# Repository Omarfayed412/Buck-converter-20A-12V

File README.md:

# Buck-converter-20A-12-V
DC DC step down buck converter 12v 20A  
Feel fee to contact me for the design files

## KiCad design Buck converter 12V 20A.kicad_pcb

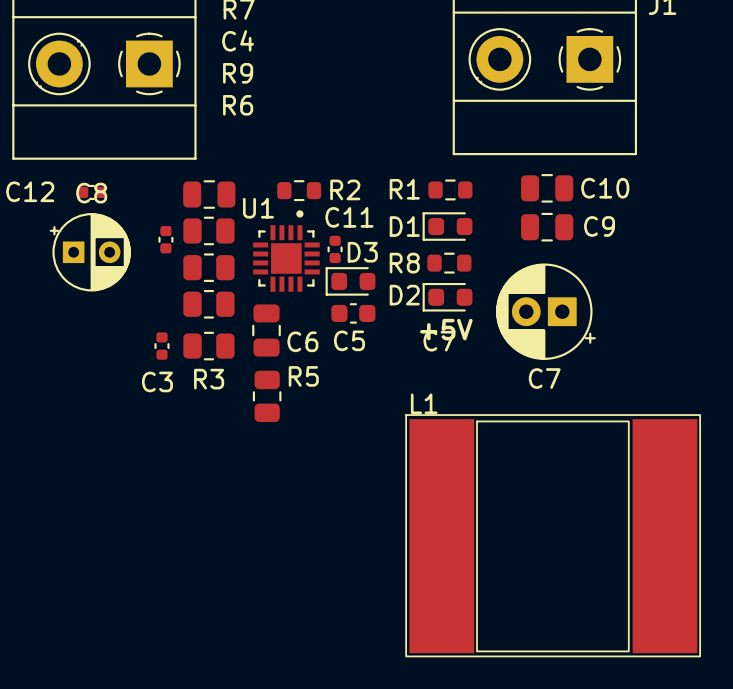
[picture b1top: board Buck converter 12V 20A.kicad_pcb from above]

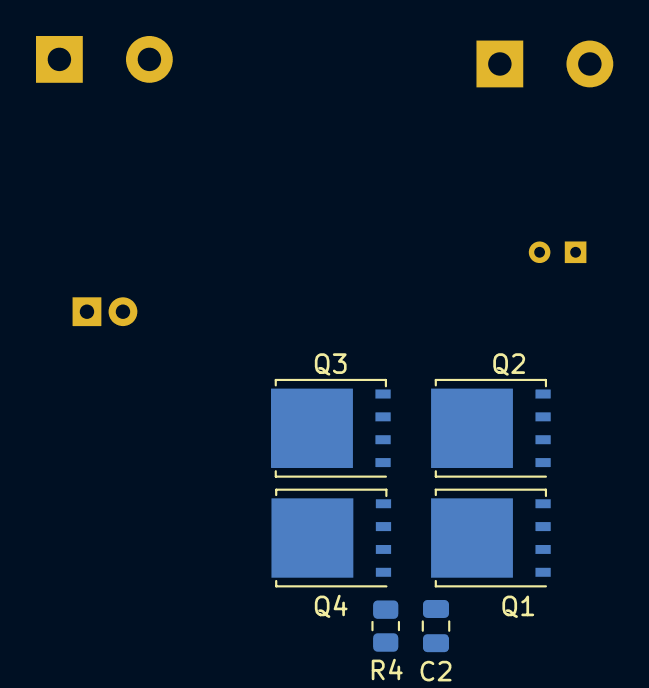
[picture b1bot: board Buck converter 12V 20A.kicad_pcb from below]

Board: 4 copper layers, 32 parts (6 on the bottom side), 20 nets, no tracks yet.

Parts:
C1: 0.047uF; C_0805_2012Metric
C2: 100pF; C_0805_2012Metric
C3: 220pf; C_0402_1005Metric
C4: 1nF; C_0402_1005Metric
C5: 1uF; C_0603_1608Metric
C6: 4.7uF; C_0805_2012Metric
C7: 330uF; CP_Radial_D5.0mm_P2.00mm
C8: 220uF; CP_Radial_D4.0mm_P2.00mm
C9, C10: 100nF; C_0805_2012Metric
C11, C12: 100nF; C_0402_1005Metric
D1: Green Led; LED_0603_1608Metric
D2: Yellow Led; LED_0603_1608Metric
D3: D_Small; D_0603_1608Metric
J1, J2: Screw_Terminal_01x02; TerminalBlock_Phoenix_MKDS-1,5-2_1x02_P5.00mm_Horizontal
L1: 3.3uH; L_Wuerth_HCM-1240
Q1, Q2, Q3, Q4: CSD17579Q3A; TDSON-8-1
R1, R8: 330R; R_0603_1608Metric
R2: 39K; R_0603_1608Metric
R3, R5: 5.1K; R_0805_2012Metric
R4: 22R; R_0805_2012Metric
R6, R7: 43.2K; R_0805_2012Metric
R9: 2.26K; R_0805_2012Metric
U1: QFN50P300X300X100-17N

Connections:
LGATE/OCS: Q1.4 (G), Q2.4 (G), R3.2, U1.8
+5V: C6.2, D3.2 (A), R8.1, U1.9
+12V: C7.1, C9.2, C10.2, J1.1, L1.2
BOOT: C5.2, D3.1 (K), U1.13
COMP: R7.2, U1.5
EXTBIAS: C1.2, C6.1, C7.2, C8.2, C9.1, C10.1, C11.1, C12.1, D1.1 (K), D2.1 (K), J1.2, J2.1, Q1.1 (S), Q1.2 (S), Q1.3 (S), Q2.1 (S), Q2.2 (S), Q2.3 (S), R2.2, R3.1, R4.1, R9.2
FB: C3.1, C4.2, R6.1, R9.1, U1.6
GND: U1.1, U1.7, U1.15, U1.17
ISEN: R5.2, U1.10
unnamed: C2.2, R4.2
unnamed: C3.2, R6.2
unnamed: C4.1, R7.1
unnamed: D1.2 (A), R1.2
unnamed: D2.2 (A), R8.2
PGOOD: R1.1, U1.2
PHASE: C2.1, C5.1, L1.1, Q1.5 (D), Q2.5 (D), Q3.1 (S), Q3.2 (S), Q3.3 (S), Q4.1 (S), Q4.2 (S), Q4.3 (S), R5.1, U1.11
RT: R2.1, U1.3
SS/TRK: C1.1, U1.4
UGATE: Q3.4 (G), Q4.4 (G), U1.12
VCC: C8.1, C11.2, C12.2, J2.2, Q3.5 (D), Q4.5 (D), U1.14

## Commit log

2023-03-25 PCB Layout and Schematic
    Added PCB design and schematic files
2023-03-25 Photos
    Here you can see the 3D model of the converter
2023-11-23 Added all the design files for Kicad
